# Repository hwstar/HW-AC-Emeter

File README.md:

**HW-AC-Emeter**
==========
This is the hardware implementation for my Atmel 90E24 power line monitor project. The Atmel 90E24 is a complete energy management solution on a chip. It allows
voltage, current, true power, apparent power, reactive power, power factor, phase angle, and line frequency to be accurately measured. Additionally it can measure
energy and with firmware, you can convert the energy pulses into kilowatt hours.

**Features:**

This board contains an ESP12 module, and an Atmel 90E24 Energy monitor chip.
The board can be powered from any floating voltage source from 5V to 12V. You can optionally stuff an ESP8266 or an 8 pin connector for use with an AVR (Arduino board) or other
microprocessor which has 3 free GPIO pins. The board partially shown on the far right is used to isolate the serial data signals from the ESP8266 from mains potential to protect your computer (see NB below).
I have a separate project on Github for the [isolated USB serial port](http://github.com/hwstar/ISO-Port) 

The board is inserted into a the live (phase) and neutral leads going to a a load which runs on mains voltages.

There is a 1 milliohm current shunt on the live  side of the connections. This allows up to 24 amps to be measured.

NB: See the disclaimer below. This project is not for beginners. THE LOGIC GROUND FOR THE ATMEL 90E24 IS CONNECTED DIRECTLY TO THE AC LIVE LEAD. This means you must heed the following warnings:

1. If you want to use test equipment on this project, an isolation transformer with floating live and neutral leads is ABSOLUTELY REQUIRED if
you want to keep your scope or other grounded test equipment from being BLOWN UP. 

2. The SPI signals going to your microprocessor are not isolated from mains so your whole system will
be at line potential. Hooking these up to something which is not floating WILL cause everything connected to be DESTROYED.

3. The serial data signals on the ESP8266 version are also not isolated and are at line potential. It is absolutely required that you use an isolated USB serial interface to prevent your computer
from being BLOWN UP.

4. The power supply for Atmel 90E24 must be floating. Do not use your lab power supply or any other power supply which is not floating. Use an ungrounded 5 volt wall wart for testing.

**EDA Software**

This board was designed using KICAD. 

**Calibration**

This is the challenging part. I took some shortcuts and cut some corners. Read the 90E24 data sheet about how to go about this correctly. You need to have some way of presenting known AC loads to the unit, and correlating the results seen in the registers. 
I used a 60 watt bulb as a resistive load. This is really far from ideal as your wall socket mains voltage will vary enough to make the effort challenging and error-prone. If you have access to a stable AC power
source (K$) and precision resistive and reactive AC loads (K$), then the calibration will be much easier. The firmware will save calibration  values to non volatile memory. 

Here is my procedure for the ESP8266 version (which can probably be improved)

1. With an AC source connected no load connected, calibrate the RMS voltage by writing test values to  the Ugain register address 0x31. Example mqtt command: 
{"command":"register","addr":"31","value":"XXXX"} Where XXXX is a 4 digit hex number. Read back voltage values using the query command, and adjust Ugain until you achieve reasonable correlation. It helps to do this
when your mains voltage is the most stable (Early in the morning). The Ugain calibration values on I saw were between 0x6410 and 0x6460
2. Next, read the current with a load disconnected, and note that there is a small offset on Irms. We need to zero out this offset before we calibrate the current. 
We will need to write values to the IoffsetL register at address 0x35. The values I saw were between 0xF7E0 and 0xF8A0.
3. Connect a resistive load and an accurate current meter such as a true RMS 5 1/2 digit DMM. Adjust the value in the Igain register 0x32 so that the reading on the accurate current meter matches
the Irms value returned by the query command. The calibration values for the Igain register I saw were between 0x4A00 and  0x4AC0.
4. Make sure the PstartTH is set to its default value of 0x8BD in register 0x27. 
5. Disconnect any load. Write 0x400 into the PNolTh register at address 0x28. This prevents the unit from metering at very low currents like when there is no load connected.
6. Make sure the Lphi register at address 0x24  is set to 0. Reactive load calibration is a future improvement to this procedure. 
7. Connect a known resistive load which is switched off. Reset the kwh accumulator in the firmware using the MQTT command {"command":"resetkwh"}. Arm a stopwatch. 
Turn on the load and start the stopwatch simultaneously. Run for 6 minutes, and turn off the load. Note the kWh returned with a query command. This will be 1/10 of the desired value. If it is off, 
adjust the value in the Lgain register at address 0x23, reset the kwh accumulator, and repeat until correlation is acheived. The values I saw were between 0xF200 and 0xF300.

Note that this procedure does not encompass using small power mode as recommended in the datasheet.

There are 2 registers used for adjusting the reactive measurements. Lphi (0x24) which adjusts the phase angle and power factor, and QoffsetL (0x38) which adjusts reactive power (Qmean) offset. 
Once the calibration procedure above is completed, adjust Lphi to get the power factor to match a calibrated meter.

**Board Size**

5cm x 10cm

**Firmware**

The AVR firmware for this project can be found [here](https://github.com/hwstar/FW-AC-Emeter)
The ESP8266 firmware for this project can be found [here](https://github.com/hwstar/FW-AC-Emeter-ESP8266)

**LICENSE**

Creative Commons Attribution Share-Alike license. (CC-BY-SA)

**Disclaimer**

Build and use at your own risk. This board uses potentially lethal mains voltages. 

I will not be responsible for any damages including but not limited to: errors or omissions, loss of life, or property damage. You have been warned.

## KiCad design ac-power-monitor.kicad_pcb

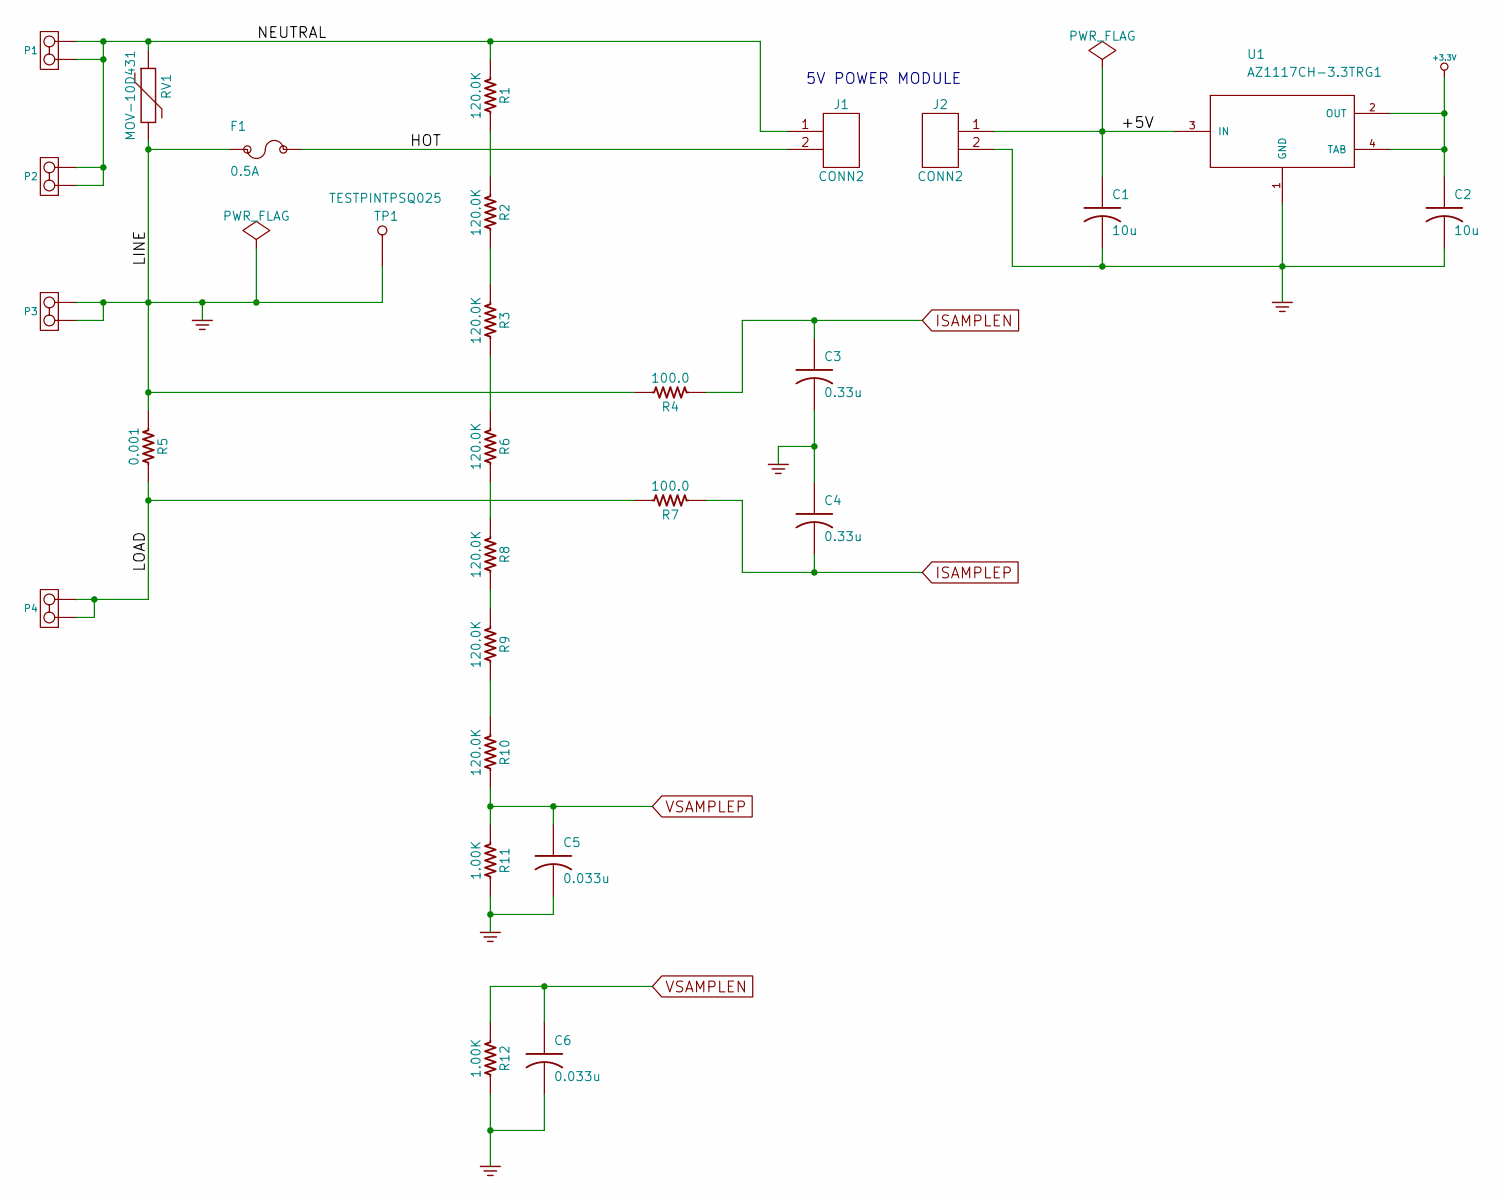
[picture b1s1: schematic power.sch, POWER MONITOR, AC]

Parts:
C1, C2: 10u; CC0805; PartNumber 800004-106
C3, C4: 0.33u; CC0603; PartNumber 800000-334
C5, C6: 0.033u; CC0603; PartNumber 800000-333
F1: 0.5A; BELFUSE_MRT; PartNumber 800125-500
J1: CONN2; JST_B3B_SPECIAL; PartNumber 800124-101
J2: CONN2; JST_B2B_XH_A; PartNumber 800114-102
P1, P2, P3, P4: FASTON_1; KEYSTONE_1287-ST; PartNumber 800157-101
R1, R2, R3, R6, R8, R9, R10: 120.0K; RC0603; PartNumber 800024-120
R4, R7: 100.0; RC0603; PartNumber 800021-100
R5: 0.001; RC0603; PartNumber 800163-101
R11, R12: 1.00K; RC0603; PartNumber 800022-100
RV1: MOV-10D431; VARISTOR-10D; PartNumber 800164-101
TP1: TESTPINTPSQ025; TESTPIN
U1: AZ1117CH-3.3TRG1; SOT-223-SAR; PartNumber 800130-101

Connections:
+3.3V: C2.1, U1.2 (OUT), U1.4 (TAB); also elsewhere on the board
/Power/+5V: C1.1, J2.1, U1.3 (IN)
/Power/HOT: F1.2, J1.2
/Power/LOAD: P4.1, P4.2, R5.2, R7.2
/Power/NEUTRAL: J1.1, P1.1, P1.2, P2.1, P2.2, R1.1, RV1.1
GND: C1.2, C2.2, C3.2, C4.1, C5.2, C6.2, F1.1, J2.2, P3.1, P3.2, R4.2, R5.1, R11.2, R12.2, RV1.2, TP1.1, U1.1 (GND); also elsewhere on the board
ISAMPLEN: C3.1, R4.1; also elsewhere on the board
ISAMPLEP: C4.2, R7.1; also elsewhere on the board
unnamed: R1.2, R2.1
unnamed: R2.2, R3.1
unnamed: R3.2, R6.1
unnamed: R6.2, R8.1
unnamed: R8.2, R9.1
unnamed: R9.2, R10.1
VSAMPLEN: C6.1, R12.1; also elsewhere on the board
VSAMPLEP: C5.1, R10.2, R11.1; also elsewhere on the board

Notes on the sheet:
5V POWER MODULE

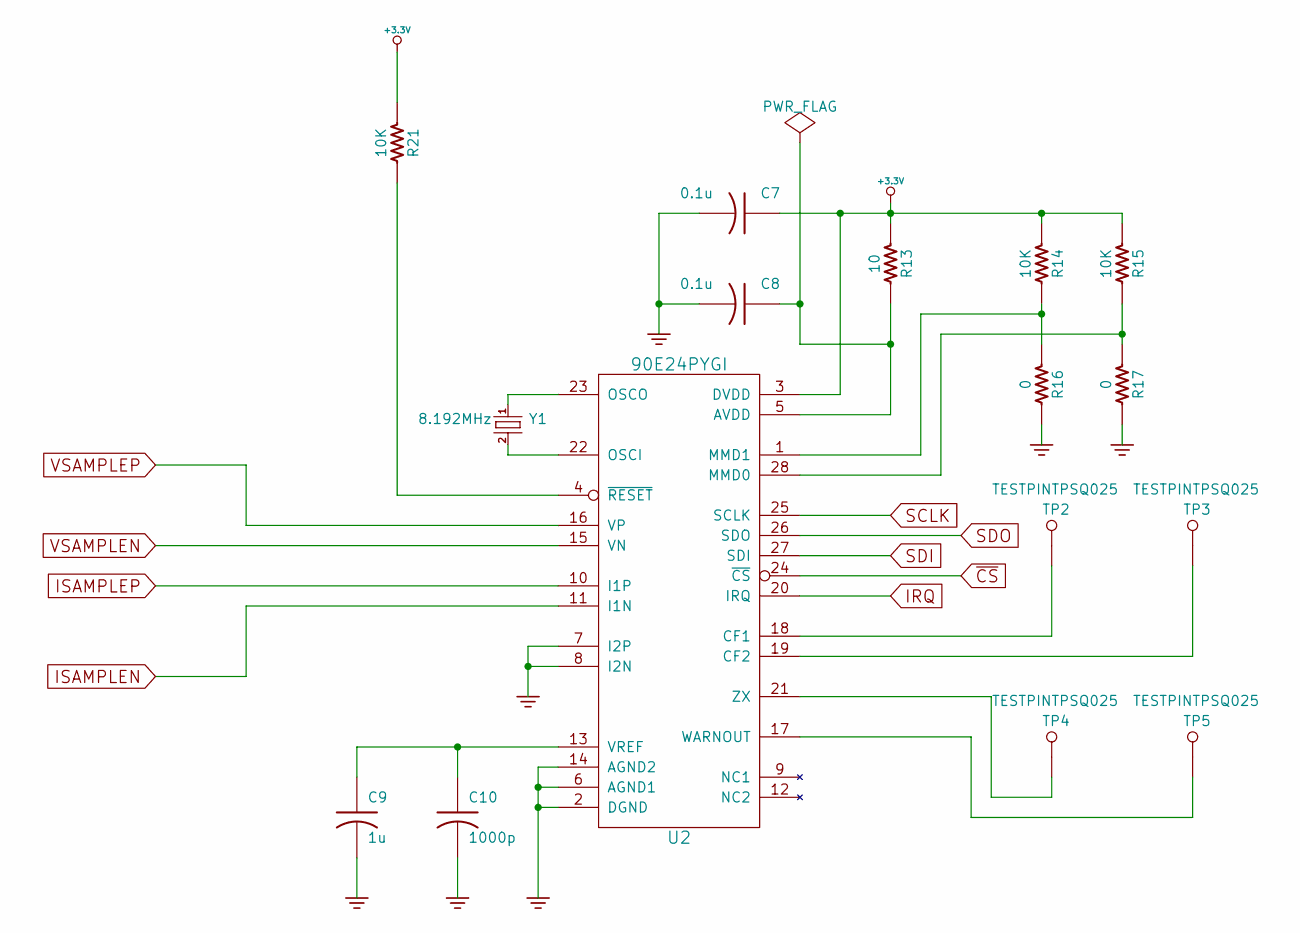
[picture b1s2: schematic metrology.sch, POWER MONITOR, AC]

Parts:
C7, C8: 0.1u; CC0603; PartNumber 800000-104
C9: 1u; CC0603; PartNumber 800001-105
C10: 1000p; CC0603; PartNumber 800002-102
R13: 10; RC0603; PartNumber 800010-100
R14, R15, R21: 10K; RC0603; PartNumber 800010-103
R16, R17: 0; RC0805; PartNumber 800011-000
TP2, TP3, TP4, TP5: TESTPINTPSQ025; TESTPAD
U2: 90E24PYGI; SSOP28-SAR; PartNumber 800159-101
Y1: 8.192MHz; HC49US-SAR; PartNumber 800108-819

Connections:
+3.3V: C7.1, R13.1, R14.1, R15.1, R21.1, U2.3 (DVDD); also elsewhere on the board
GND: C7.2, C8.2, C9.2, C10.2, R16.2, R17.2, U2.2 (DGND), U2.6 (AGND1), U2.7 (I2P), U2.8 (I2N), U2.14 (AGND2); also elsewhere on the board
IRQ: U2.20 (IRQ); also elsewhere on the board
ISAMPLEN: U2.11 (I1N); also elsewhere on the board
ISAMPLEP: U2.10 (I1P); also elsewhere on the board
unnamed: C8.1, R13.2, U2.5 (AVDD)
unnamed: C9.1, C10.1, U2.13 (VREF)
unnamed: R14.2, R16.1, U2.1 (MMD1)
unnamed: R15.2, R17.1, U2.28 (MMD0)
unnamed: R21.2, U2.4 (~RESET)
unnamed: TP2.1, U2.18 (CF1)
unnamed: TP3.1, U2.19 (CF2)
unnamed: TP4.1, U2.21 (ZX)
unnamed: TP5.1, U2.17 (WARNOUT)
unnamed: U2.22 (OSCI), Y1.2
unnamed: U2.23 (OSCO), Y1.1
SCLK: U2.25 (SCLK); also elsewhere on the board
SDI: U2.27 (SDI); also elsewhere on the board
SDO: U2.26 (SDO); also elsewhere on the board
VSAMPLEN: U2.15 (VN); also elsewhere on the board
VSAMPLEP: U2.16 (VP); also elsewhere on the board
~CS: U2.24 (~CS); also elsewhere on the board

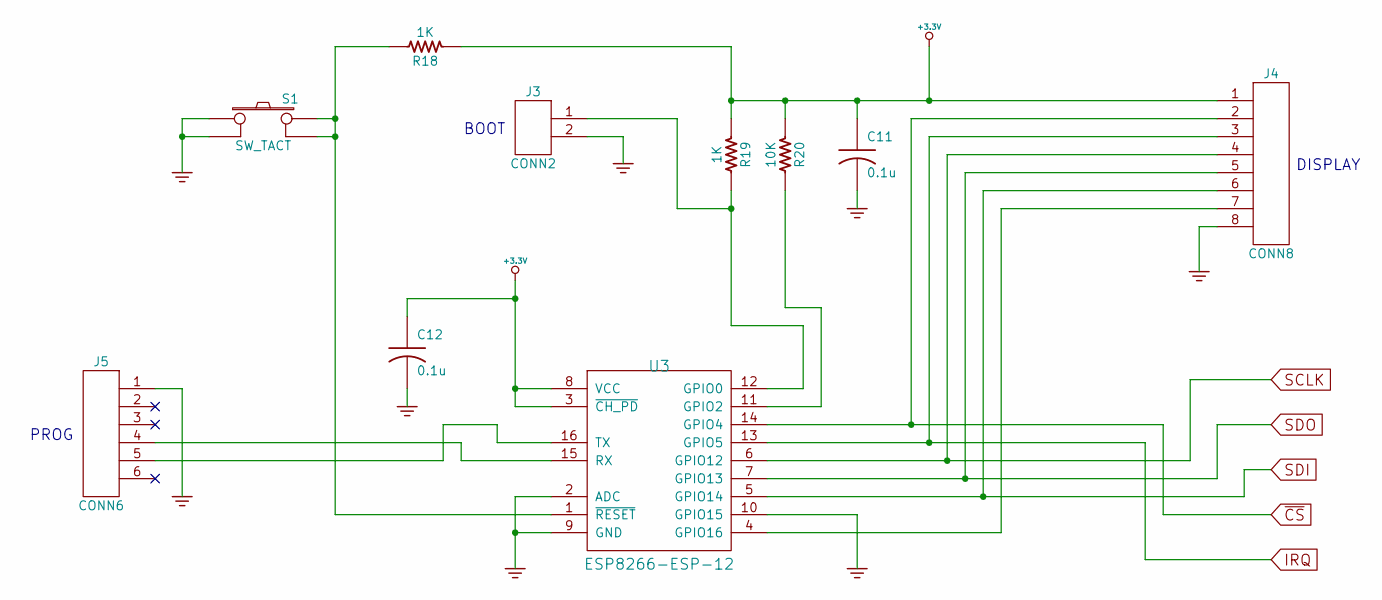
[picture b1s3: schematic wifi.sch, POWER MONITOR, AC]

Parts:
C11, C12: 0.1u; CC0603; PartNumber 800000-104
J3: CONN2; BERG2; PartNumber 800116-102
J4: CONN8; JST_B8B_XH_A; PartNumber 800114-108
J5: CONN6; BERG6; PartNumber 800116-106
R18, R19: 1K; RC0603; PartNumber 800010-102
R20: 10K; RC0603; PartNumber 800010-103
S1: SW_TACT; SW_TACT_6MM; PartNumber 800107-101
U3: ESP8266-ESP-12; ESP8266-ESP12; PartNumber 800106-101

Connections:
+3.3V: C11.1, C12.1, J4.1, R18.1, R19.1, R20.1, U3.3 (~CH_PD), U3.8 (VCC); also elsewhere on the board
GND: C11.2, C12.2, J3.2, J4.8, J5.1, S1.1, S1.2, U3.2 (ADC), U3.9 (GND), U3.10 (GPIO15); also elsewhere on the board
IRQ: J4.3, U3.13 (GPIO5); also elsewhere on the board
unnamed: J3.1, R19.2, U3.12 (GPIO0)
unnamed: J4.7, U3.4 (GPIO16)
unnamed: J5.4, U3.15 (RX)
unnamed: J5.5, U3.16 (TX)
unnamed: R18.2, S1.3, S1.4, U3.1 (~RESET)
unnamed: R20.2, U3.11 (GPIO2)
SCLK: J4.4, U3.6 (GPIO12); also elsewhere on the board
SDI: J4.6, U3.5 (GPIO14); also elsewhere on the board
SDO: J4.5, U3.7 (GPIO13); also elsewhere on the board
~CS: J4.2, U3.14 (GPIO4); also elsewhere on the board

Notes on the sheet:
BOOT
DISPLAY
PROG

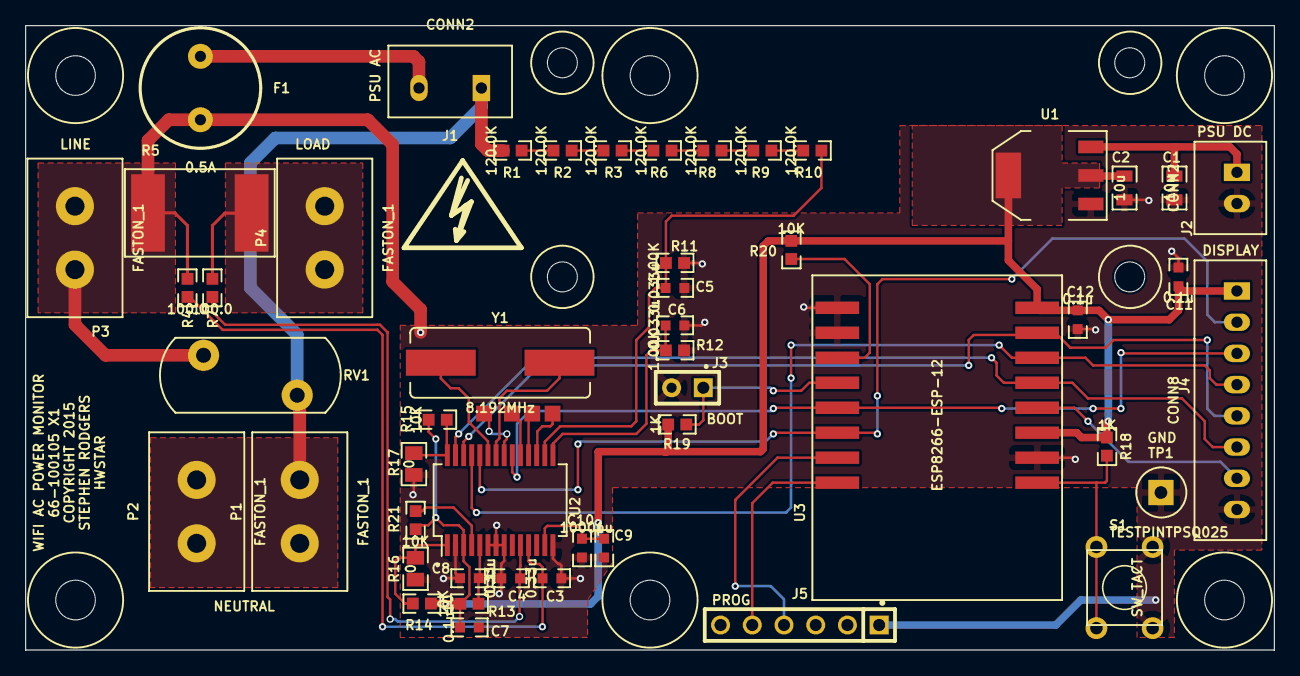
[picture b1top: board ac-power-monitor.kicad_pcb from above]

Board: 2 copper layers, 100.0 x 50.0 mm, 65 parts (0 on the bottom side), 38 nets.

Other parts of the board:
MTG-HOLE-125-RING-300, MTG-HOLE-125-RING-300#2, MTG-HOLE-125-RING-300#3, MTG-HOLE-125-RING-300#4, MTG-HOLE-125-RING-300#5, MTG-HOLE-125-RING-300#6: VAL**; MTG-HOLE-125-RING-300
MTG-HOLE-M2-RING-5MM, MTG-HOLE-M2-RING-5MM#2, MTG-HOLE-M2-RING-5MM#3, MTG-HOLE-M2-RING-5MM#4: VAL**; MTG-HOLE-M2-RING-5MM
Sym: Symbol_HighVoltage_Type2_SilkTop_VerySmall

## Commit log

2015-09-18 Initial checkin rev X1
2015-09-18 Add README.md and acpowermonitor.jpg files
2015-09-18 Add rework pictures
2015-09-18 Remove rework 2 file
2015-09-22 update picture
2015-10-04 Add calibration procedure
2015-10-13 Update README.md with reactive power info
2015-10-16 Release revision A schematic, board, and BOM. Update picture to show revision A board. Remove X1 rework instructions from README.md.
2015-10-16 Add gerbers, remove .cmp from tracking, update pdf, net, pro.
2015-10-16 Update revision letters on schematic pages

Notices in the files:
ac-power-monitor.kicad_pcb:
COPYRIGHT 2015
